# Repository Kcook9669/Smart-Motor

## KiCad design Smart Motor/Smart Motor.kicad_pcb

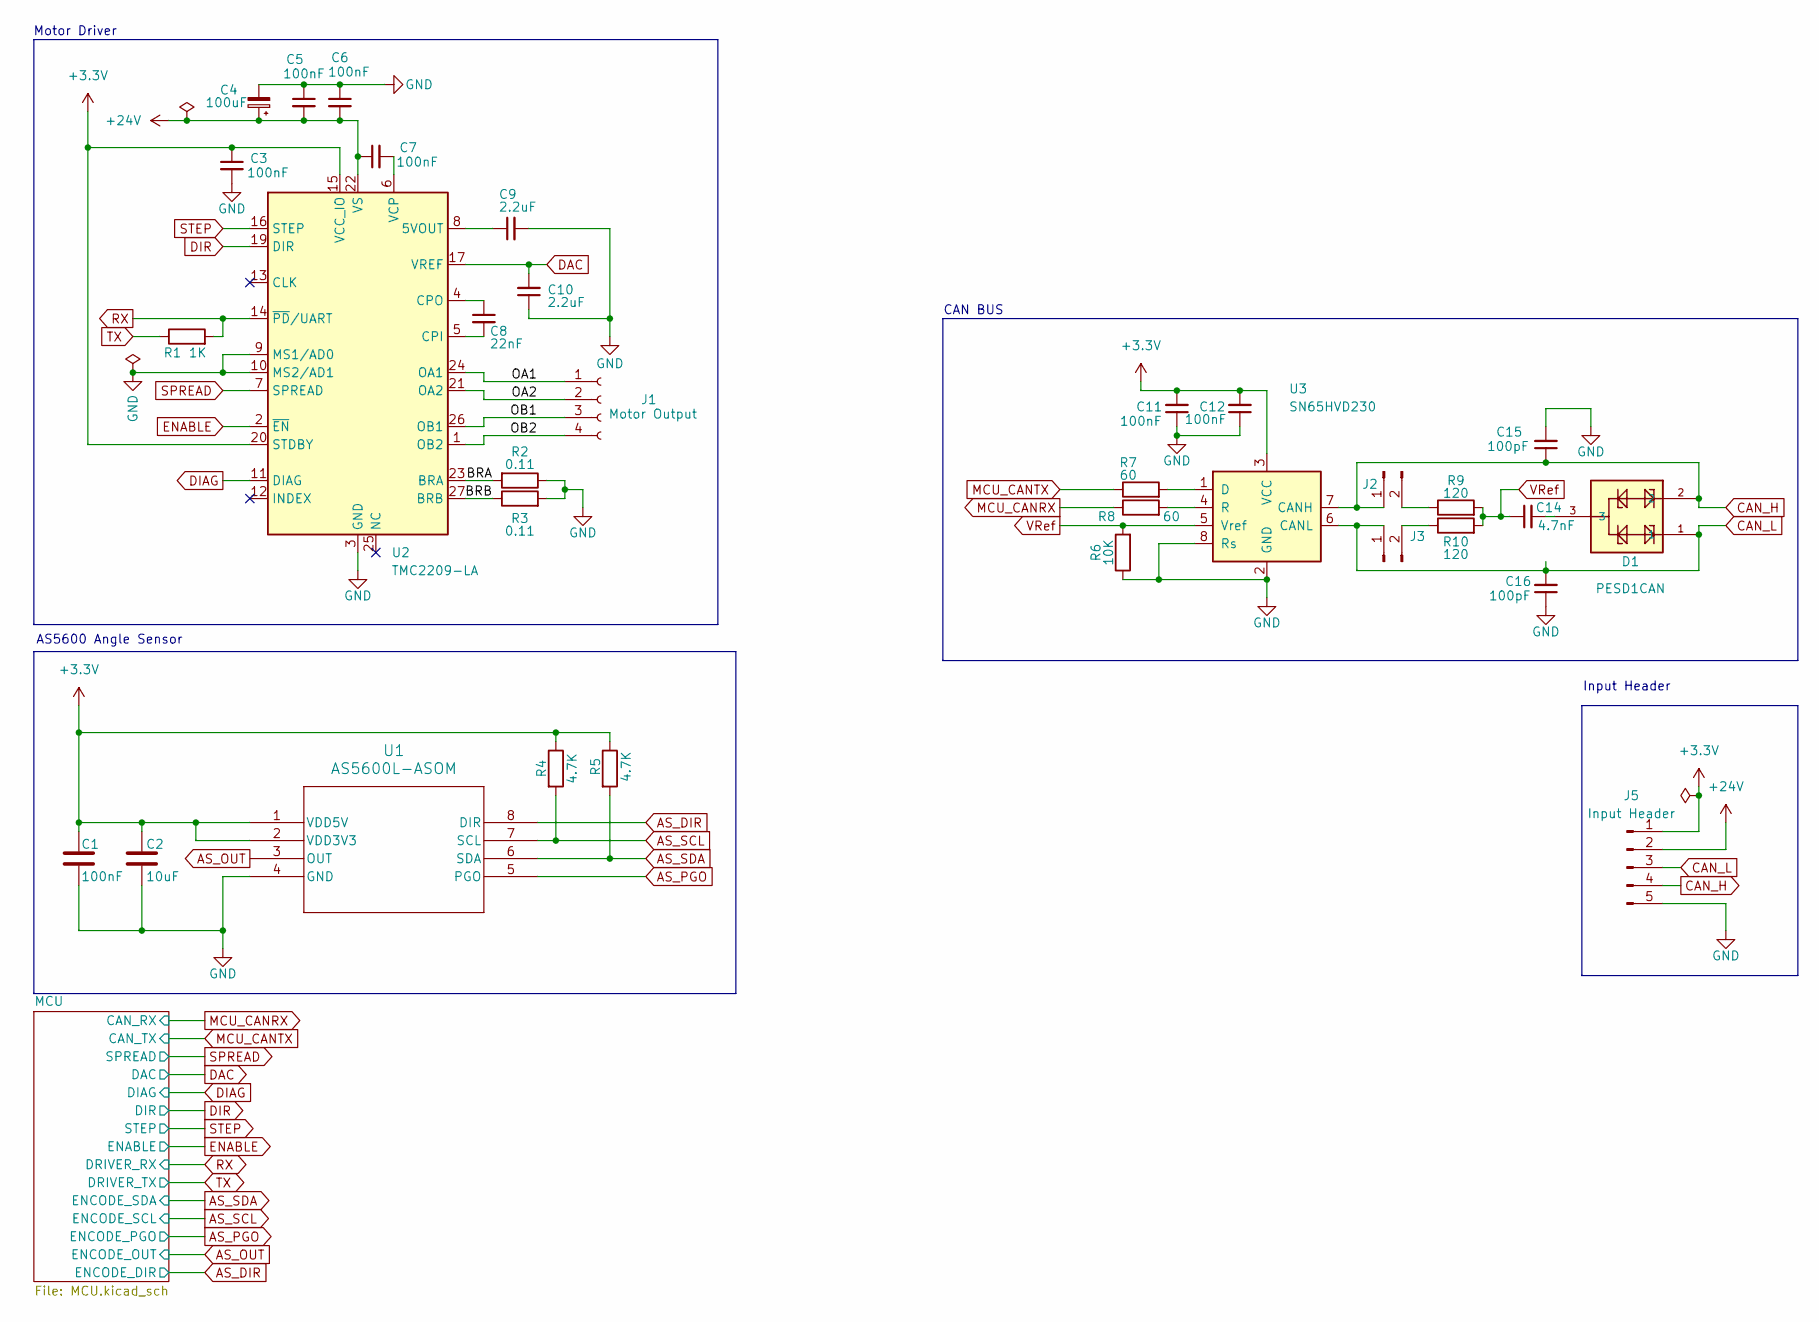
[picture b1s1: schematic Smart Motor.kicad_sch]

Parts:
C1, C3, C11, C12: 100nF; C_0603_1608Metric_Pad1.08x0.95mm_HandSolder
C2: 10uF; C_0603_1608Metric_Pad1.08x0.95mm_HandSolder
C4: 100uF; C_1210_3225Metric
C5, C6, C7: 100nF; C_1210_3225Metric
C8: 22nF; C_0603_1608Metric_Pad1.08x0.95mm_HandSolder
C9, C10: 2.2uF; C_0603_1608Metric_Pad1.08x0.95mm_HandSolder
C14: 4.7nF; C_0603_1608Metric_Pad1.08x0.95mm_HandSolder
C15, C16: 100pF; C_0603_1608Metric_Pad1.08x0.95mm_HandSolder
D1: PESD1CAN; SOT23-3
J1: Motor Output; JST_XH_B4B-XH-A_1x04_P2.50mm_Vertical
J2, J3: Conn_01x02_Pin; PinHeader_1x02_P2.54mm_Vertical
J5: Input Header; JST_XH_B5B-XH-A_1x05_P2.50mm_Vertical
R1: 1K; R_0603_1608Metric_Pad0.98x0.95mm_HandSolder
R2, R3: 0.11; R_0603_1608Metric_Pad0.98x0.95mm_HandSolder
R4, R5: 4.7K; R_0603_1608Metric_Pad0.98x0.95mm_HandSolder
R6: 10K; R_0603_1608Metric_Pad0.98x0.95mm_HandSolder
R7, R8: 60; R_0603_1608Metric_Pad0.98x0.95mm_HandSolder
R9, R10: 120; R_0603_1608Metric_Pad0.98x0.95mm_HandSolder
U1: AS5600L-ASOM; AS5600L-ASOM_AMS-M
U2: TMC2209-LA; VQFN-28-1EP_5x5mm_P0.5mm_EP3.7x3.7mm_ThermalVias
U3: SN65HVD230; SOIC-8_3.9x4.9mm_P1.27mm

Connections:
+3.3V: C1.2, C2.2, C3.1, C11.2, C12.2, J5.1, R4.1, R5.1, U1.1 (VDD5V), U1.2 (VDD3V3), U2.15 (VCC_IO), U2.20 (STDBY), U3.3 (VCC); also elsewhere on the board
+24V: C4.1, C5.2, C6.2, C7.1, J5.2, U2.22 (VS), U2.28 (VS)
/BRA: R2.2, U2.23 (BRA)
/BRB: R3.1, U2.27 (BRB)
/OA1: J1.1, U2.24 (OA1)
/OA2: J1.2, U2.21 (OA2)
/OB1: J1.3, U2.26 (OB1)
/OB2: J1.4, U2.1 (OB2)
AS_DIR: U1.8 (DIR); also elsewhere on the board
AS_OUT: U1.3 (OUT); also elsewhere on the board
AS_PGO: U1.5 (PGO); also elsewhere on the board
AS_SCL: R4.2, U1.7 (SCL); also elsewhere on the board
AS_SDA: R5.2, U1.6 (SDA); also elsewhere on the board
CAN_H: C15.1, D1.2, J2.1, J5.4, U3.7 (CANH)
CAN_L: C16.2, D1.1, J3.1, J5.3, U3.6 (CANL)
DAC: C10.2, U2.17 (VREF); also elsewhere on the board
DIAG: U2.11 (DIAG); also elsewhere on the board
DIR: U2.19 (DIR); also elsewhere on the board
ENABLE: U2.2 (~EN); also elsewhere on the board
GND: C1.1, C2.1, C3.2, C4.2, C5.1, C6.1, C9.2, C10.1, C11.1, C12.1, C15.2, C16.1, J5.5, R2.1, R3.2, R6.1, U1.4 (GND), U2.3 (GND), U2.9 (MS1/AD0), U2.10 (MS2/AD1), U2.18 (GND), U2.29 (GND), U3.2 (GND), U3.8 (Rs); also elsewhere on the board
MCU_CANRX: R8.1; also elsewhere on the board
MCU_CANTX: R7.1; also elsewhere on the board
unnamed: C14.2, D1.3
unnamed: J2.2, R9.1
unnamed: J3.2, R10.1
unnamed: C9.1, U2.8 (5VOUT)
unnamed: C8.2, U2.5 (CPI)
unnamed: C8.1, U2.4 (CPO)
unnamed: C7.2, U2.6 (VCP)
unnamed: R7.2, U3.1 (D)
unnamed: R8.2, U3.4 (R)
RX: R1.2, U2.14 (~PD/UART); also elsewhere on the board
SPREAD: U2.7 (SPREAD); also elsewhere on the board
STEP: U2.16 (STEP); also elsewhere on the board
TX: R1.1; also elsewhere on the board
VRef: C14.1, R6.2, R9.2, R10.2, U3.5 (Vref)

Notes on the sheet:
Input Header
Motor Driver
AS5600 Angle Sensor
CAN BUS

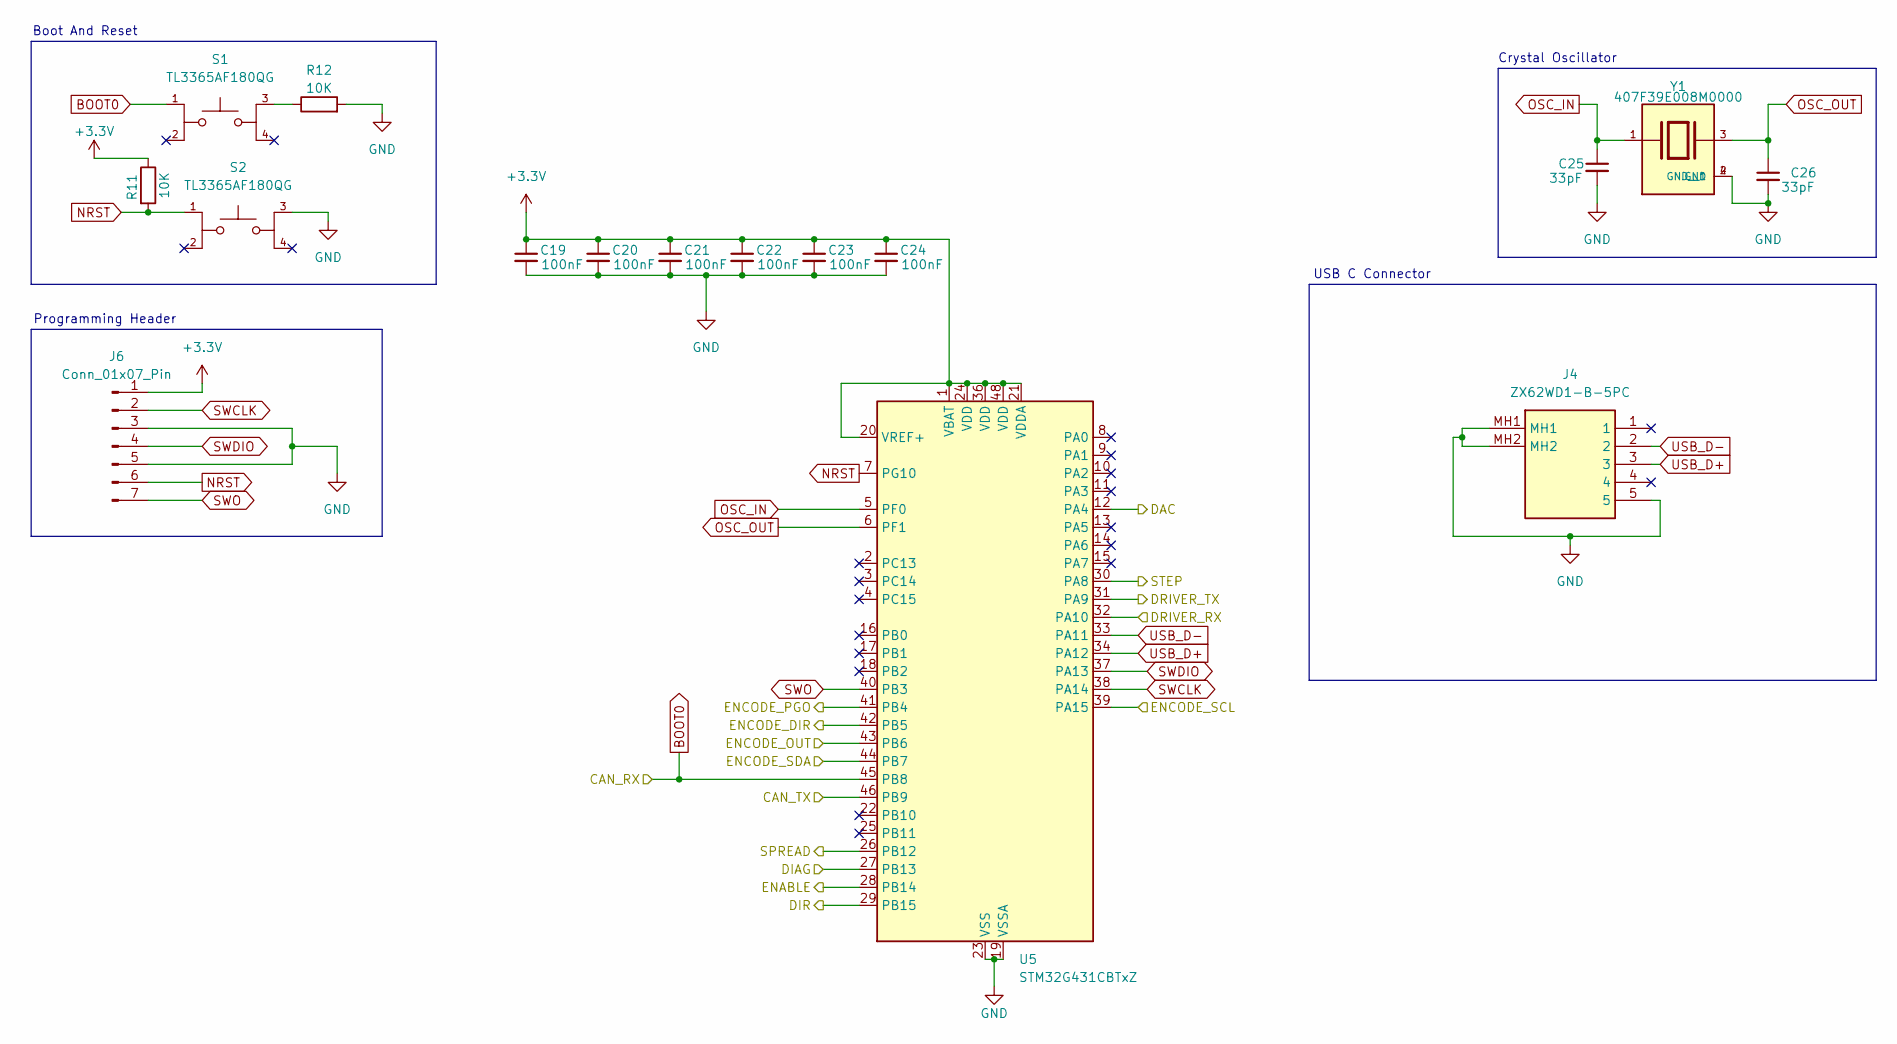
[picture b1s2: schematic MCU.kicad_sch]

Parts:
C19, C20, C21, C22, C23, C24: 100nF; C_0603_1608Metric_Pad1.08x0.95mm_HandSolder
C25, C26: 33pF; C_0603_1608Metric_Pad1.08x0.95mm_HandSolder
J4: ZX62WD1-B-5PC; ZX62WD1B5PC; Mouser Part Number 798-ZX62WD1-B-5PC
J6: Conn_01x07_Pin; PinHeader_1x07_P2.54mm_Vertical
R11, R12: 10K; R_0603_1608Metric_Pad0.98x0.95mm_HandSolder
S1, S2: TL3365AF180QG; PARTREV A
U5: STM32G431CBTxZ; LQFP-48_7x7mm_P0.5mm
Y1: 407F39E008M0000; XTAL_407F39E008M0000; PARTREV N/A

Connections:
+3.3V: C19.1, C20.1, C21.1, C22.1, C23.1, C24.1, J6.1, R11.1, U5.1 (VBAT), U5.20 (VREF+), U5.21 (VDDA), U5.24 (VDD), U5.36 (VDD), U5.48 (VDD); also elsewhere on the board
AS_DIR: U5.42 (PB5); also elsewhere on the board
AS_OUT: U5.43 (PB6); also elsewhere on the board
AS_PGO: U5.41 (PB4); also elsewhere on the board
AS_SCL: U5.39 (PA15); also elsewhere on the board
AS_SDA: U5.44 (PB7); also elsewhere on the board
DAC: U5.12 (PA4); also elsewhere on the board
DIAG: U5.27 (PB13); also elsewhere on the board
DIR: U5.29 (PB15); also elsewhere on the board
ENABLE: U5.28 (PB14); also elsewhere on the board
GND: C19.2, C20.2, C21.2, C22.2, C23.2, C24.2, C25.2, C26.2, J4.5, J4.MH1, J4.MH2, J6.3, J6.5, R12.2, S2.3, U5.19 (VSSA), U5.23 (VSS), U5.35 (VSS), U5.47 (VSS), Y1.2 (GND), Y1.4 (GND__1); also elsewhere on the board
MCU_CANRX: S1.1, U5.45 (PB8); also elsewhere on the board
MCU_CANTX: U5.46 (PB9); also elsewhere on the board
NRST: J6.6, R11.2, S2.1, U5.7 (PG10)
unnamed: R12.1, S1.3
OSC_IN: C25.1, U5.5 (PF0), Y1.1
OSC_OUT: C26.1, U5.6 (PF1), Y1.3
RX: U5.32 (PA10); also elsewhere on the board
SPREAD: U5.26 (PB12); also elsewhere on the board
STEP: U5.30 (PA8); also elsewhere on the board
SWCLK: J6.2, U5.38 (PA14)
SWDIO: J6.4, U5.37 (PA13)
SWO: J6.7, U5.40 (PB3)
TX: U5.31 (PA9); also elsewhere on the board
USB_D+: J4.3, U5.34 (PA12)
USB_D-: J4.2, U5.33 (PA11)

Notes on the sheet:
Crystal Oscillator
Boot And Reset
Programming Header
USB C Connector

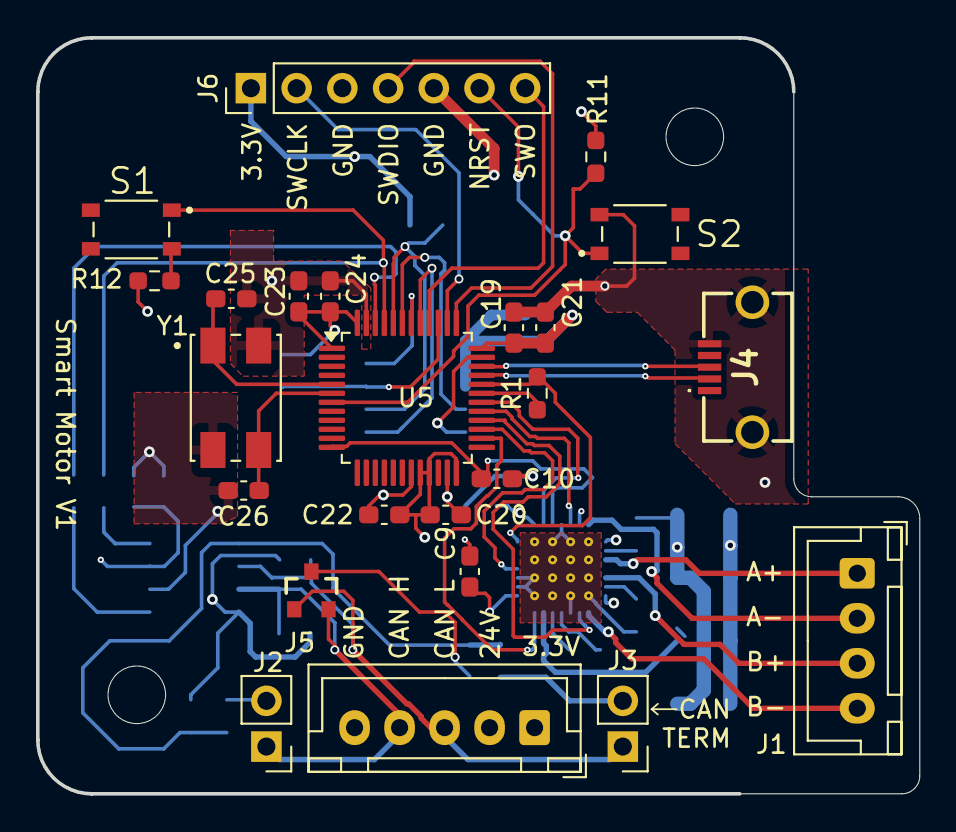
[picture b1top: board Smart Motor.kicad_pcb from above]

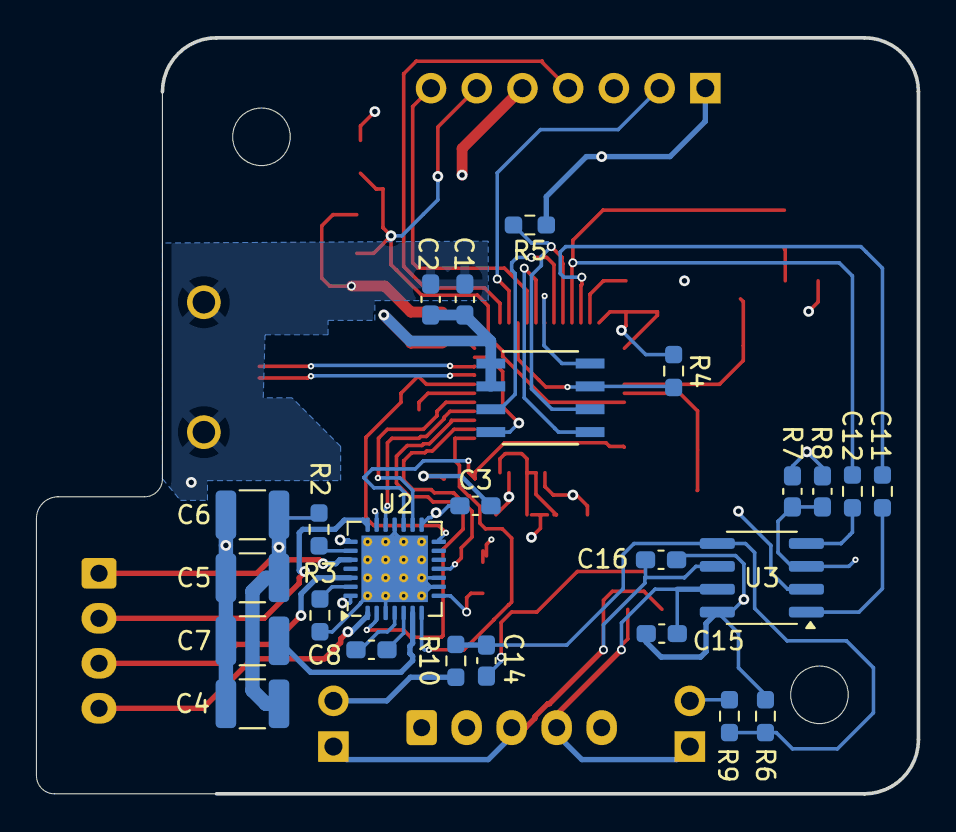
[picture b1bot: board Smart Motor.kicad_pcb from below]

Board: 4 copper layers, 48.9 x 42.0 mm, 49 parts (25 on the bottom side), 45 nets.

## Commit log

2025-07-24 Finished initial design of motor PCB
